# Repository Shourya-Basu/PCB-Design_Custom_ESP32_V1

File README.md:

---

### Tech Stack

- Schematic – The blueprint stage where logical connections between components are defined using symbols, pins, and nets to create a functional electrical map.

- PCB Routing – The physical design process of laying down copper tracks (traces) on the board to connect components while adhering to design rules like clearance, trace width, and signal integrity.

- KiCad – An open-source EDA suite used for schematic capture and PCB layout, offering powerful tools for 3D visualization and Gerber file generation.
---

### Images

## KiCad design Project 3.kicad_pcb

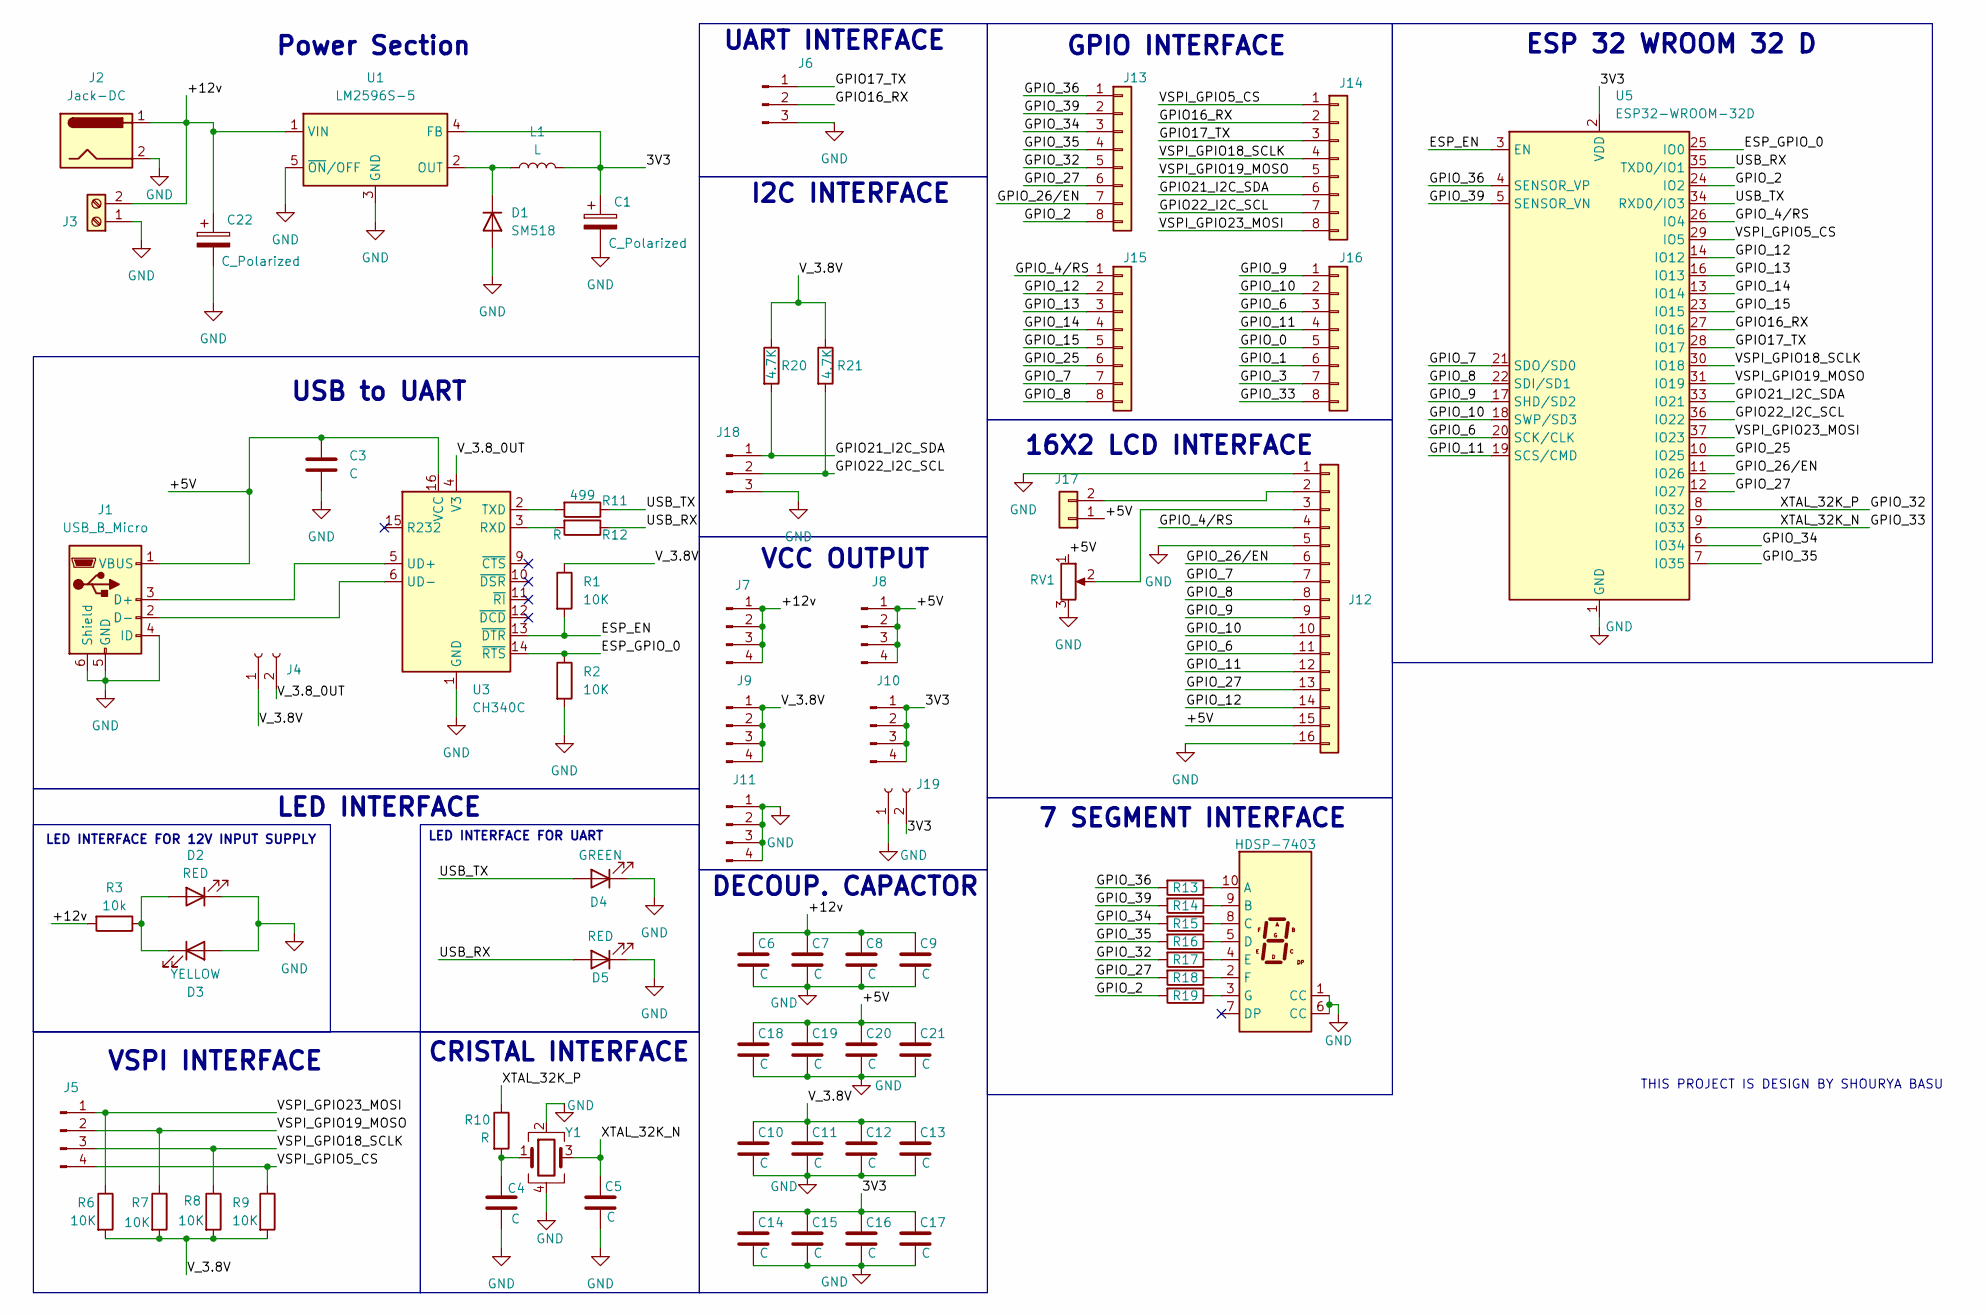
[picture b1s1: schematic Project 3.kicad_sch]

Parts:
C1, C22: C_Polarized; C_0805_2012Metric_Pad1.18x1.45mm_HandSolder
C3: C; C_0805_2012Metric
C4, C5, C6, C7, C8, C9, C10, C11, C12, C13, C14, C15, C16, C17, C18, C19, C20, C21: C; C_0805_2012Metric_Pad1.18x1.45mm_HandSolder
D1: SM518; D_0805_2012Metric_Pad1.15x1.40mm_HandSolder
D2, D5: RED; LED_0805_2012Metric_Pad1.15x1.40mm_HandSolder
D3: YELLOW; LED_0805_2012Metric_Pad1.15x1.40mm_HandSolder
D4: GREEN; LED_0805_2012Metric_Pad1.15x1.40mm_HandSolder
J1: USB_B_Micro; USB_Micro-AB_Molex_47590-0001
J2: Jack-DC; BarrelJack_SwitchcraftConxall_RAPC10U_Horizontal
J3: Screw_Terminal_01x02; TerminalBlock_bornier-2_P5.08mm
J4: Conn_01x02_Socket; PinSocket_1x02_P2.54mm_Vertical
J5, J7, J8, J9, J10, J11: Conn_01x04_Pin; FanPinHeader_1x04_P2.54mm_Vertical
J6, J18: Conn_01x03_Pin; FanPinHeader_1x03_P2.54mm_Vertical
J12: Conn_01x16; PinHeader_1x16_P2.54mm_Vertical
J13, J14, J15, J16: Conn_01x08; Molex_KK-254_AE-6410-08A_1x08_P2.54mm_Vertical
J17: Conn_01x02; PinHeader_1x02_P2.54mm_Vertical
J19: Conn_01x02_Socket; PinHeader_1x02_P2.54mm_Vertical
L1: L; L_0805_2012Metric_Pad1.05x1.20mm_HandSolder
R1, R2, R6, R7, R8, R9: 10K; R_0805_2012Metric_Pad1.20x1.40mm_HandSolder
R3: 10k; R_0805_2012Metric_Pad1.20x1.40mm_HandSolder
R10, R12: R; R_0805_2012Metric_Pad1.20x1.40mm_HandSolder
R11, R13, R14, R15, R16, R17, R18, R19: 499; R_0805_2012Metric_Pad1.20x1.40mm_HandSolder
R20, R21: 4.7K; R_0805_2012Metric_Pad1.20x1.40mm_HandSolder
RV1: R_Potentiometer; Potentiometer_Vishay_148-149_Single_Horizontal
U1: LM2596S-5; TO-263-5_TabPin3
U3: CH340C; SOIC-16_3.9x9.9mm_P1.27mm
U4: HDSP-7403; HDSP-7401
U5: ESP32-WROOM-32D
Y1: Crystal_GND24; Crystal_SMD_0603-4Pin_6.0x3.5mm

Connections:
/3V3: C1.1, C14.1, C15.1, C16.1, C17.1, J10.1, J10.2, J10.3, J10.4, J19.2, L1.2, U1.4 (FB), U5.2 (VDD)
/+5V: C3.1, C18.1, C19.1, C20.1, C21.1, J1.1 (VBUS), J8.1, J8.2, J8.3, J8.4, J12.15, J17.1, RV1.1, U3.16 (VCC)
/+12v: C6.1, C7.1, C8.1, C9.1, C22.1, J2.1, J3.2, J7.1, J7.2, J7.3, J7.4, R3.2, U1.1 (VIN)
/ESP_EN: R1.2, U3.13 (~DTR), U5.3 (EN)
/ESP_GPIO_0: R2.1, U3.14 (~RTS), U5.25 (IO0)
/GPIO16_RX: J6.2, J14.2, U5.27 (IO16)
/GPIO17_TX: J6.1, J14.3, U5.28 (IO17)
/GPIO21_I2C_SDA: J14.6, J18.1, R20.2, U5.33 (IO21)
/GPIO22_I2C_SCL: J14.7, J18.2, R21.2, U5.36 (IO22)
/GPIO_0: J16.5
/GPIO_1: J16.6
/GPIO_2: J13.8, R19.2, U5.24 (IO2)
/GPIO_3: J16.7
/GPIO_4/RS: J12.4, J15.1, U5.26 (IO4)
/GPIO_6: J12.11, J16.3, U5.20 (SCK/CLK)
/GPIO_7: J12.7, J15.7, U5.21 (SDO/SD0)
/GPIO_8: J12.8, J15.8, U5.22 (SDI/SD1)
/GPIO_9: J12.9, J16.1, U5.17 (SHD/SD2)
/GPIO_10: J12.10, J16.2, U5.18 (SWP/SD3)
/GPIO_11: J12.12, J16.4, U5.19 (SCS/CMD)
/GPIO_12: J12.14, J15.2, U5.14 (IO12)
/GPIO_13: J15.3, U5.16 (IO13)
/GPIO_14: J15.4, U5.13 (IO14)
/GPIO_15: J15.5, U5.23 (IO15)
/GPIO_25: J15.6, U5.10 (IO25)
/GPIO_26/EN: J12.6, J13.7, U5.11 (IO26)
/GPIO_27: J12.13, J13.6, R18.2, U5.12 (IO27)
/GPIO_32: J13.5, R10.1, R17.2, U5.8 (IO32)
/GPIO_33: C5.1, J16.8, U5.9 (IO33), Y1.3
/GPIO_34: J13.3, R15.2, U5.6 (IO34)
/GPIO_35: J13.4, R16.2, U5.7 (IO35)
/GPIO_36: J13.1, R13.2, U5.4 (SENSOR_VP)
/GPIO_39: J13.2, R14.2, U5.5 (SENSOR_VN)
/USB_RX: D5.2 (A), R12.1, U5.35 (TXD0/IO1)
/USB_TX: D4.2 (A), R11.1, U5.34 (RXD0/IO3)
/VSPI_GPIO5_CS: J5.4, J14.1, R9.1, U5.29 (IO5)
/VSPI_GPIO18_SCLK: J5.3, J14.4, R8.1, U5.30 (IO18)
/VSPI_GPIO19_MOSO: J5.2, J14.5, R7.1, U5.31 (IO19)
/VSPI_GPIO23_MOSI: J5.1, J14.8, R6.1, U5.37 (IO23)
/V_3.8V: C10.1, C11.1, C12.1, C13.1, J4.1, J9.1, J9.2, J9.3, J9.4, R1.1, R6.2, R7.2, R8.2, R9.2, R20.1, R21.1
/V_3.8_0UT: J4.2, U3.4 (V3)
GND: C1.2, C3.2, C4.2, C5.2, C6.2, C7.2, C8.2, C9.2, C10.2, C11.2, C12.2, C13.2, C14.2, C15.2, C16.2, C17.2, C18.2, C19.2, C20.2, C21.2, C22.2, D1.2 (A), D2.1 (K), D3.2 (A), D4.1 (K), D5.1 (K), J1.4 (ID), J1.5 (GND), J1.6 (Shield), J2.2, J3.1, J6.3, J11.1, J11.2, J11.3, J11.4, J12.1, J12.5, J12.16, J18.3, J19.1, R2.2, RV1.3, U1.3 (GND), U1.5 (~ON/OFF), U3.1 (GND), U4.1 (CC), U4.6 (CC), U5.1 (GND), U5.15 (GND), U5.38 (GND), U5.39 (GND), Y1.2, Y1.4
unnamed: C4.1, R10.2, Y1.1
unnamed: D1.1 (K), L1.1, U1.2 (OUT)
unnamed: D2.2 (A), D3.1 (K), R3.1
unnamed: J1.3 (D+), U3.5 (UD+)
unnamed: J1.2 (D-), U3.6 (UD-)
unnamed: J12.2, J17.2
unnamed: J12.3, RV1.2
unnamed: R12.2, U3.3 (RXD)
unnamed: R11.2, U3.2 (TXD)
unnamed: R13.1, U4.10 (A)
unnamed: R14.1, U4.9 (B)
unnamed: R15.1, U4.8 (C)
unnamed: R16.1, U4.5 (D)
unnamed: R17.1, U4.4 (E)
unnamed: R18.1, U4.2 (F)
unnamed: R19.1, U4.3 (G)

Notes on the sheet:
VSPI INTERFACE
ESP 32 WROOM 32 D
I2C INTERFACE
THIS PROJECT IS DESIGN BY SHOURYA BASU
16X2 LCD INTERFACE
7 SEGMENT INTERFACE
VCC OUTPUT
Power Section
LED INTERFACE FOR 12V INPUT SUPPLY
DECOUP. CAPACTOR
LED INTERFACE FOR UART
UART INTERFACE
LED INTERFACE
USB to UART
GPIO INTERFACE
CRISTAL INTERFACE

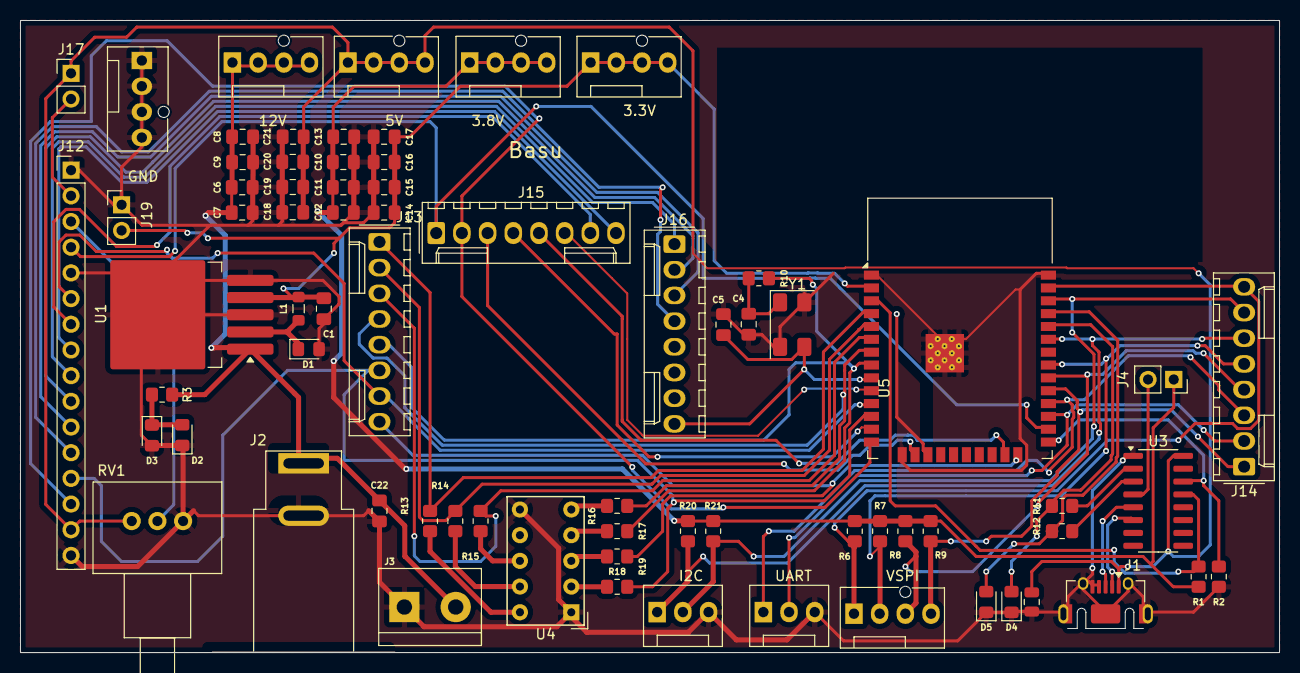
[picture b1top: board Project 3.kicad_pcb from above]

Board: 2 copper layers, 124.4 x 62.4 mm, 71 parts (0 on the bottom side), 55 nets.
